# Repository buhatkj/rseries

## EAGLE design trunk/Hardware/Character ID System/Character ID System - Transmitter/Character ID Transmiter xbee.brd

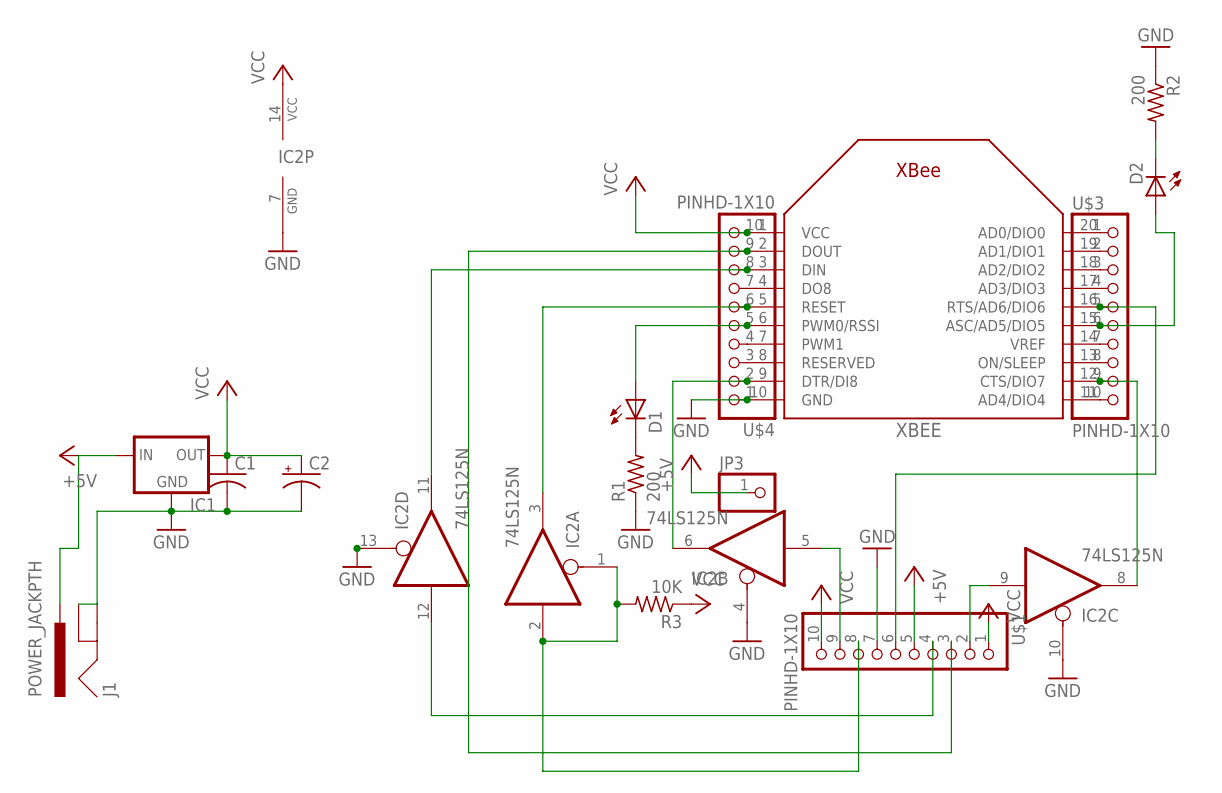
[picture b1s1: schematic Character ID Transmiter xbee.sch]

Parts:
C1: C-US025-025X050; C025-025X050
C2: CPOL-USE2.5-5; E2,5-5
D1, D2: LED3MM
IC1: MC1700; TO92
IC2: 74LS125N; DIL14
J1: POWER_JACKPTH; POWER_JACK_PTH
JP3: PINHD-1X1; 1X01
R1, R2: 200; 0207/10
R3: 10K; 0207/10
U$1, U$3, U$4: PINHD-1X10; 1X10-BIG
XBEE: XBEE

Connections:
+5V: IC1.2 (IN), J1.PWR, JP3.1, U$1.5
GND: C1.2, C2.-, IC1.1 (GND), IC2.4 (OE), IC2.7 (GND), IC2.10 (OE), IC2.13 (OE), J1.GND, J1.GNDBREAK, R1.1, R2.1, U$1.7, U$4.1, XBEE.10 (GND)
unnamed: IC2.12 (I), U$1.4
unnamed: IC2.11 (O), U$4.8, XBEE.3 (DIN)
unnamed: IC2.5 (I), U$1.9
unnamed: IC2.8 (O), U$3.9, XBEE.12 (CTS/DIO7)
unnamed: D2.K (C), R2.2
unnamed: U$4.7, XBEE.4 (DO8)
unnamed: D1.A, U$4.5, XBEE.6 (PWM0/RSSI)
unnamed: D1.K (C), R1.2
unnamed: D2.A, U$3.6, XBEE.15 (ASC/AD5/DIO5)
unnamed: IC2.6 (O), U$4.2, XBEE.9 (DTR/DI8)
unnamed: U$4.3, XBEE.8 (RESERVED)
unnamed: U$4.4, XBEE.7 (PWM1)
unnamed: IC2.3 (O), U$4.6, XBEE.5 (RESET)
unnamed: U$3.1, XBEE.20 (AD0/DIO0)
unnamed: U$3.2, XBEE.19 (AD1/DIO1)
unnamed: U$3.3, XBEE.18 (AD2/DIO2)
unnamed: U$3.4, XBEE.17 (AD3/DIO3)
unnamed: U$3.7, XBEE.14 (VREF)
unnamed: U$3.8, XBEE.13 (ON/SLEEP)
unnamed: U$3.10, XBEE.11 (AD4/DIO4)
unnamed: IC2.9 (I), U$1.2
RESET: IC2.1 (OE), IC2.2 (I), R3.2, U$1.8
RTS: U$1.6, U$3.5, XBEE.16 (RTS/AD6/DIO6)
TX: U$1.3, U$4.9, XBEE.2 (DOUT)
VCC: C1.1, C2.+, IC1.3 (OUT), IC2.14 (VCC), R3.1, U$1.1, U$1.10, U$4.10, XBEE.1 (VCC)

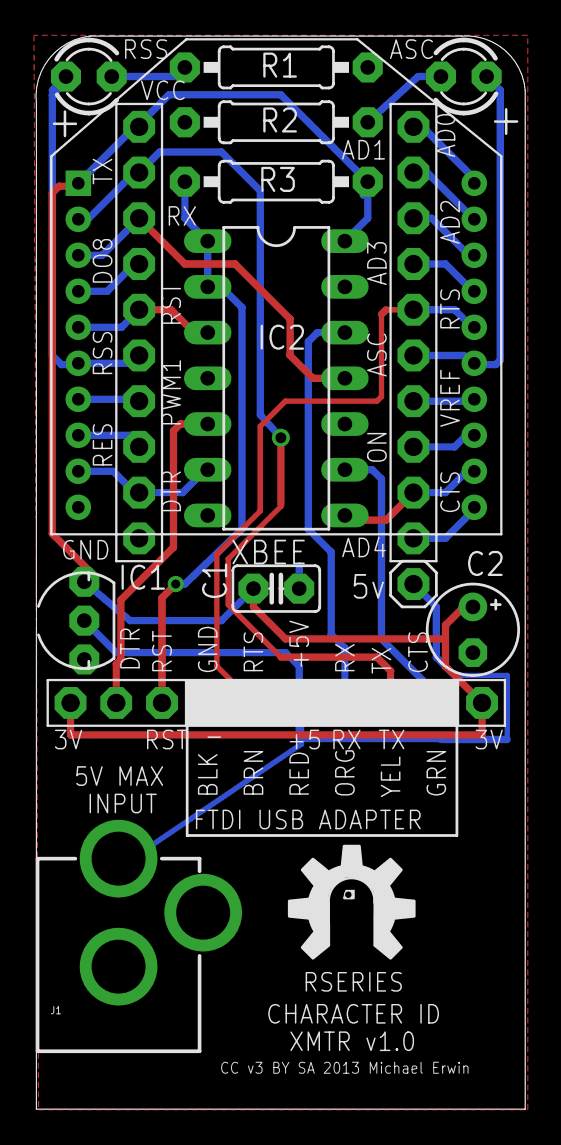
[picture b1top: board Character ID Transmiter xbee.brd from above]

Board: 2 copper layers, 27.2 x 59.6 mm, 17 parts (1 on the bottom side), 27 nets.

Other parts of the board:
U$2: RSERIES-OSHW-LOGO-LARGE
U$5: ROYAL-ENGINEERS-OF-NABOO-SMALL

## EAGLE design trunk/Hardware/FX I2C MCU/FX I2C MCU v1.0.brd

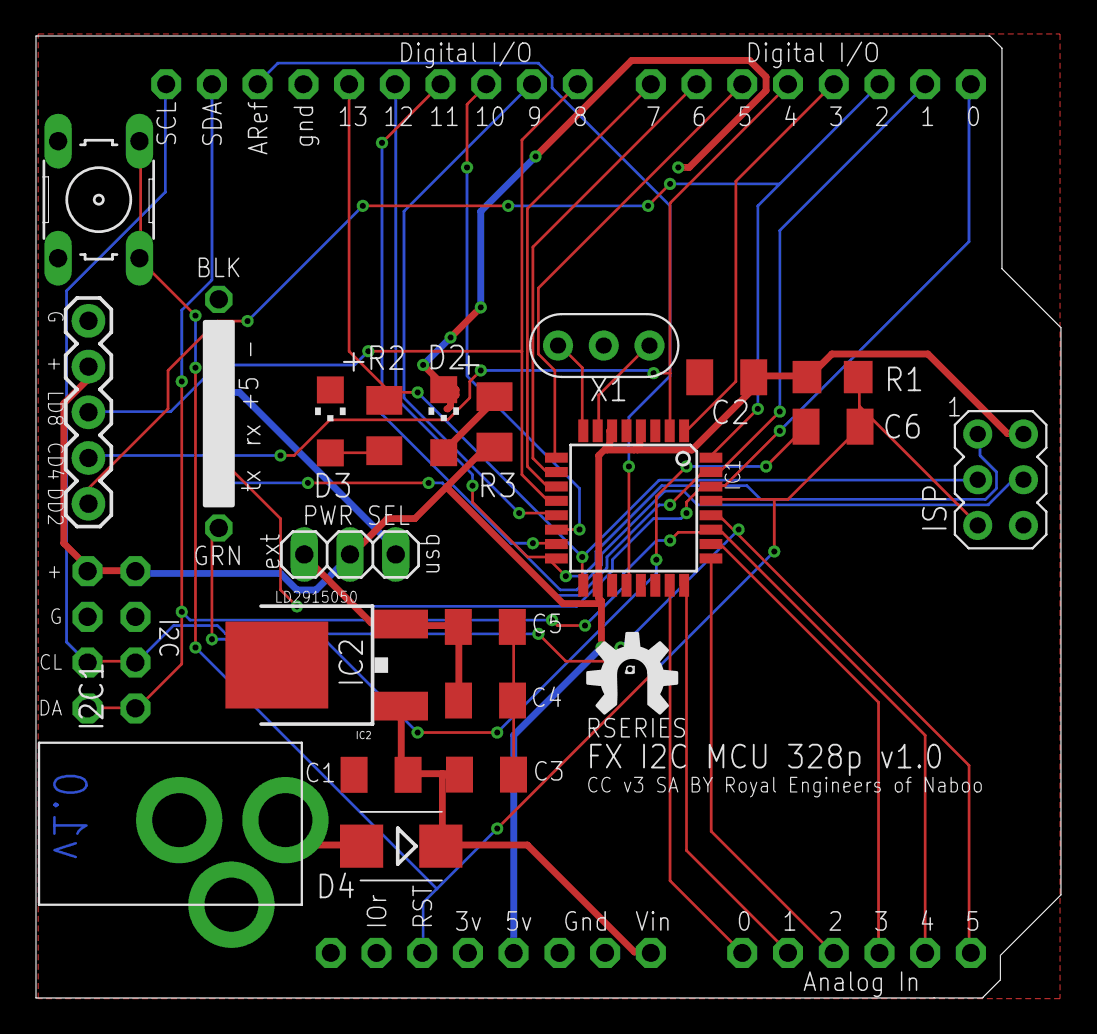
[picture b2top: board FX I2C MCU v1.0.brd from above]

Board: 2 copper layers, 56.9 x 53.4 mm, 25 parts (0 on the bottom side), 34 nets.

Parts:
C1, C2, C5, C6: 0.1uF; C1206K
C3, C4: 10uf 25V; C1206K
D2: CHIPLED_1206
D3: Green; CHIPLED_1206
D4: SMB
I2C, I2C1: 1X04-CB
IC1: MEGA48/88/168-AU; TQFP32-08
IC2: LM2931_FIXED; DPAK
ISP: AVRISP-6; AVRISP
J2: 2.1MMJACK; PJ-102A
JP7: 1X06-CLEAN
PWR_SEL: 1X03
R1: 10K; R1206
R2, R3: 1.0 K; M1206
S1: RESET; B3F-10XX
TEECES: 1X05
U1: ARDUINOR3PINSONLY; ARDUINOR3-PINSONLY
U$2: RSERIES-OSHW-LOGOMEDIUM; RSERIES-OSHW-LOGO-MEDIUM
X1: 16.00MHz; CERM_OSC

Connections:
+5V: C2.1, I2C.4, I2C1.4, IC1.4, IC1.6, IC1.18, ISP.2, PWR_SEL.2, R1.1, R3.1, TEECES.4, U1.5V
+9V: C1.1, C3.1, D4.C, IC2.1, U1.VIN
ANALOG0: IC1.23, U1.A0
ANALOG1: IC1.24, U1.A1
ANALOG2: IC1.25, U1.A2
ANALOG3: IC1.26, U1.A3
ANALOG4: I2C.1, I2C1.1, IC1.27, U1.A4, U1.SDA
ANALOG5: I2C.2, I2C1.2, IC1.28, U1.A5, U1.SCL
AREF: IC1.20, U1.AREF
DIGITAL2: IC1.32, TEECES.1, U1.D2
DIGITAL3: IC1.1, U1.D3
DIGITAL4: IC1.2, TEECES.2, U1.D4
DIGITAL5: IC1.9, U1.D5
DIGITAL6: IC1.10, U1.D6
DIGITAL7: IC1.11, U1.D7
DIGITAL8: IC1.12, TEECES.3, U1.D8
DIGITAL9: IC1.13, U1.D9
DIGITAL10: IC1.14, U1.D10
GND: C1.2, C2.2, D2.C, D3.C, I2C.3, I2C1.3, IC1.3, IC1.5, IC1.21, IC2.4, ISP.6, J2.RING, JP7.1, JP7.2, S1.1, S1.2, TEECES.5, U1.GND, U1.GND1, U1.GND2, X1.P$2
MISO: IC1.16, ISP.1, U1.D12
MOSI: IC1.15, ISP.4, U1.D11
unnamed: IC1.7, X1.P$1
unnamed: IC1.8, X1.P$3
unnamed: D2.A, R3.2
unnamed: D3.A, R2.2
unnamed: D4.A, J2.TIP
unnamed: C3.2, C4.2, C5.2
unnamed: C4.1, C5.1, IC2.3, PWR_SEL.1
RST: C6.2, IC1.29, ISP.5, R1.2, S1.3, S1.4, U1.RESET
RTS#: C6.1, JP7.6
RXD: IC1.30, JP7.4, U1.D0
SCK: IC1.17, ISP.3, R2.1, U1.D13
TXD: IC1.31, JP7.5, U1.D1
USB_5V: JP7.3, PWR_SEL.3

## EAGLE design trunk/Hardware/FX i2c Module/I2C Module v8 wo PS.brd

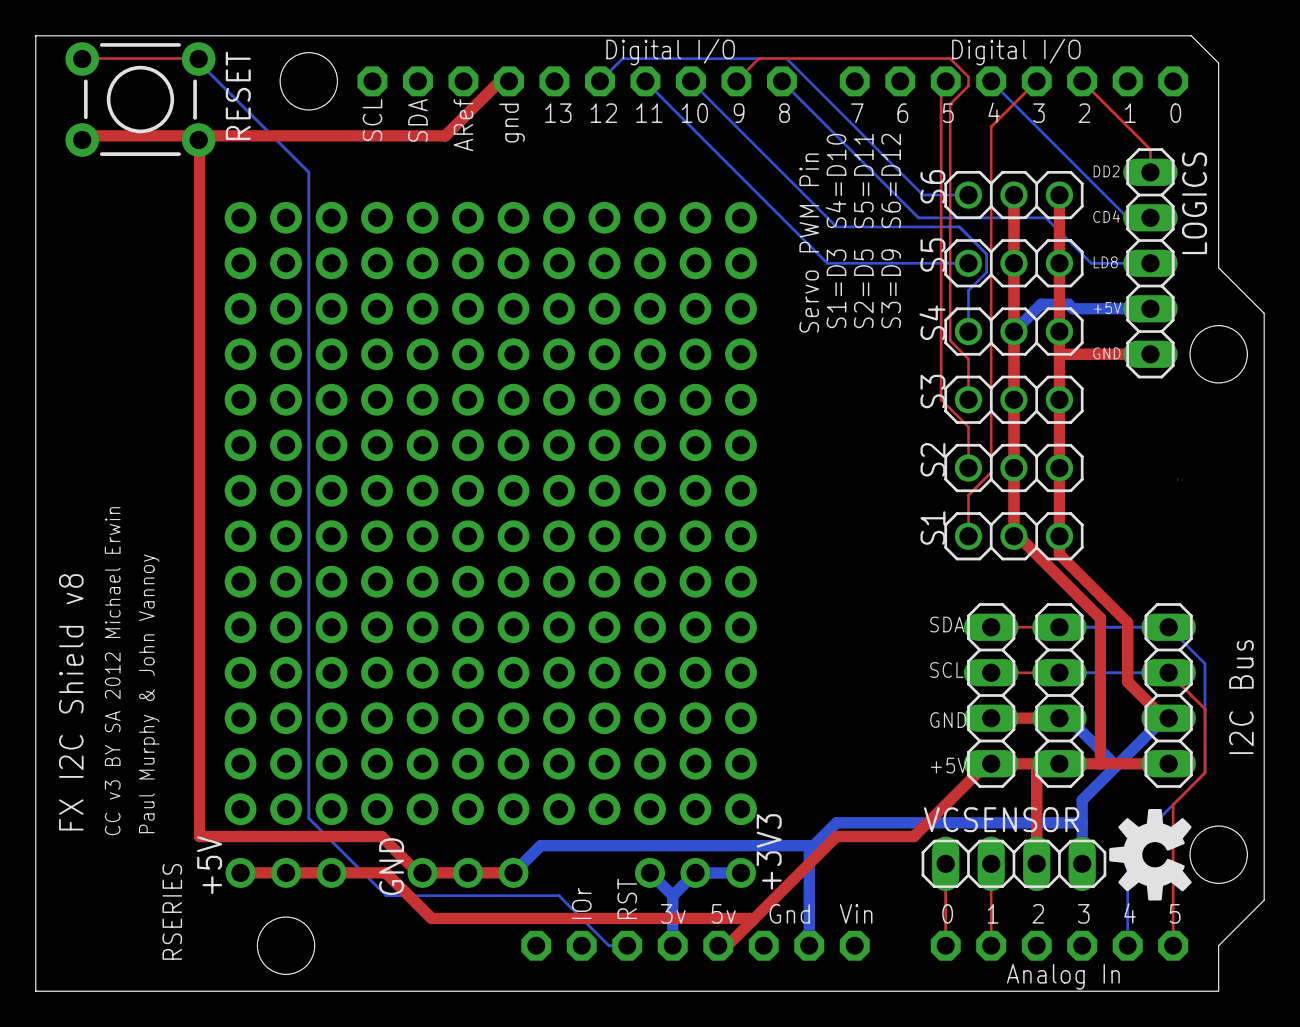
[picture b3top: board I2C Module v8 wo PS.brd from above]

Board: 2 copper layers, 68.6 x 53.3 mm, 31 parts (0 on the bottom side), 17 nets.

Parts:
+3V3, +5V: 1X03-CLEANBIG
GND: 1X03-CLEANBIG
I2C3: 1X04
JP1, JP2: 1X04
JP3, JP4, JP5, JP6, JP7, JP8, JP9, JP10, JP11, JP12, JP13, JP14, JP15, JP16: 1X12-CB
LOGICS: 1X05
RESET: TACTILE-PTH
S1, S2, S3, S4, S5, S6: 1X03
U1: ARDUINOR3-DIMENSION; ARDUINOR3
U$1: OSHW-LOGOM; OSHW-LOGO-M
VCSENSOR: 1X04

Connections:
+3V3: +3V3.1, +3V3.2, +3V3.3, U1.3V
+5V: +5V.1, +5V.2, +5V.3, I2C3.4, JP1.4, JP2.4, LOGICS.4, S1.2, S2.2, S3.2, S4.2, S5.2, S6.2, U1.5V, VCSENSOR.3
GND: GND.1, GND.2, GND.3, I2C3.3, JP1.3, JP2.3, LOGICS.5, RESET.1, RESET.2, S1.3, S2.3, S3.3, S4.3, S5.3, S6.3, U1.GND, U1.GND1, VCSENSOR.4
unnamed: U1.A0, VCSENSOR.1
unnamed: LOGICS.3, U1.D8
unnamed: U1.A1, VCSENSOR.2
unnamed: S1.1, U1.D3
unnamed: S2.1, U1.D5
unnamed: S3.1, U1.D9
unnamed: S4.1, U1.D10
unnamed: S5.1, U1.D11
unnamed: S6.1, U1.D12
unnamed: LOGICS.2, U1.D4
unnamed: LOGICS.1, U1.D2
unnamed: RESET.3, RESET.4, U1.RESET
unnamed: I2C3.2, JP1.2, JP2.2, U1.A5
unnamed: I2C3.1, JP1.1, JP2.1, U1.A4

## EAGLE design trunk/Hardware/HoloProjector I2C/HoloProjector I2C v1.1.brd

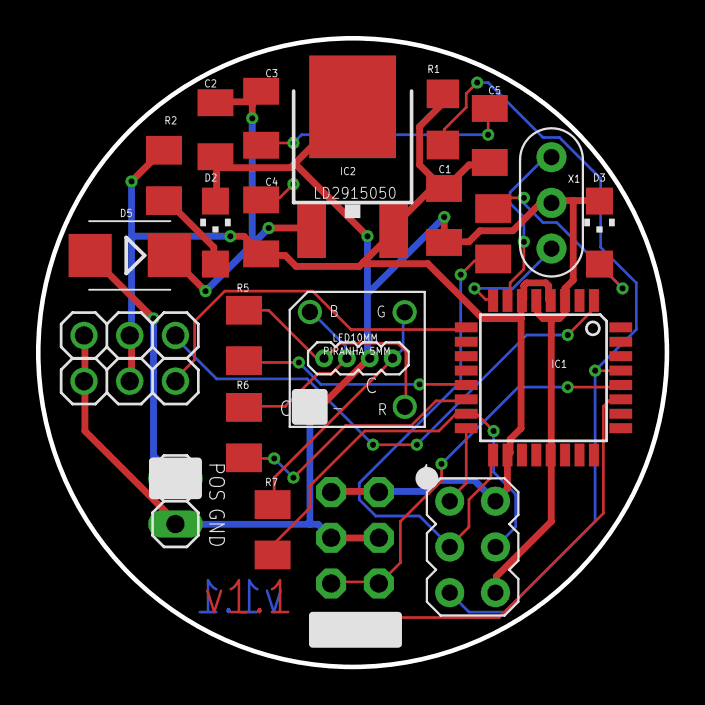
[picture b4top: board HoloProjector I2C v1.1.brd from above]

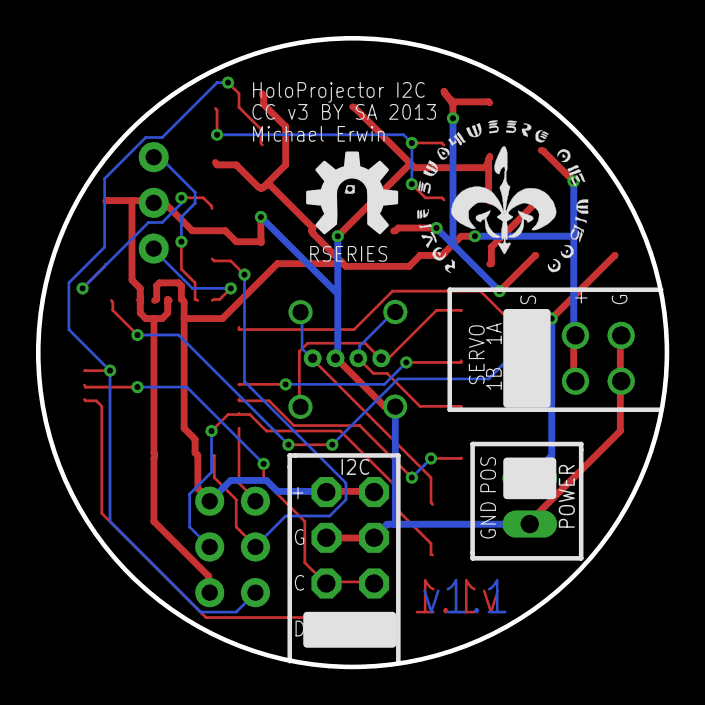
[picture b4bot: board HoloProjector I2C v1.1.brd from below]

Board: 2 copper layers, 34.9 x 34.9 mm, 27 parts (2 on the bottom side), 22 nets.

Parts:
C1, C2, C5: 0.1uF; C1206K
C3, C4: 10uf 25V; C1206K
D2: CHIPLED_1206
D3: Green; CHIPLED_1206
D5: SMB
I2C, I2C1: 1X04-CB
IC1: MEGA48/88/168-AU; TQFP32-08
IC2: LM2931_FIXED; DPAK
ICSP: AVRISP-6; AVRISP
JP1, JP2: 1X03
LED: LED_PIRANHA_5MM
LED10MM: 1X04-1.27MM
POWER: 1X02
R1: 10K; R1206
R2, R3: 1.0 K; M1206
R5, R6, R7: M1206
U$2: RSERIES-OSHW-LOGOMEDIUM; RSERIES-OSHW-LOGO-MEDIUM
U$3: ROYAL-ENGINEERS-OF-NABOOSMALL; ROYAL-ENGINEERS-OF-NABOO-SMALL
X1: 16.00MHz; CERM_OSC

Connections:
+5V: C1.1, C4.1, C5.1, I2C.4, I2C1.4, IC1.4, IC1.6, IC1.18, IC2.3, ICSP.2, JP1.2, JP2.2, R1.1, R2.1
+9V: C2.1, C3.1, D5.C, IC2.1
ANALOG4: I2C.1, I2C1.1, IC1.27
ANALOG5: I2C.2, I2C1.2, IC1.28
DIGITAL3: IC1.1, JP1.1
DIGITAL5: IC1.9, JP2.1
DIGITAL9: IC1.13, R5.2
DIGITAL10: IC1.14, R6.2
GND: C1.2, C2.2, D2.C, D3.C, I2C.3, I2C1.3, IC1.3, IC1.5, IC1.21, IC2.4, ICSP.6, JP1.3, JP2.3, LED.-, LED10MM.3, POWER.1, X1.P$2
MISO: IC1.16, ICSP.1
MOSI: IC1.15, ICSP.4, R7.2
unnamed: IC1.7, X1.P$1
unnamed: IC1.8, X1.P$3
unnamed: LED.R, LED10MM.1, R5.1
unnamed: D3.A, R3.2
unnamed: D2.A, R2.2
unnamed: D5.A, POWER.2
unnamed: LED.B, LED10MM.2, R6.1
unnamed: C3.2, C4.2, C5.2
unnamed: LED.G, LED10MM.4, R7.1
RST: IC1.29, ICSP.5, R1.2
SCK: IC1.17, ICSP.3, R3.1

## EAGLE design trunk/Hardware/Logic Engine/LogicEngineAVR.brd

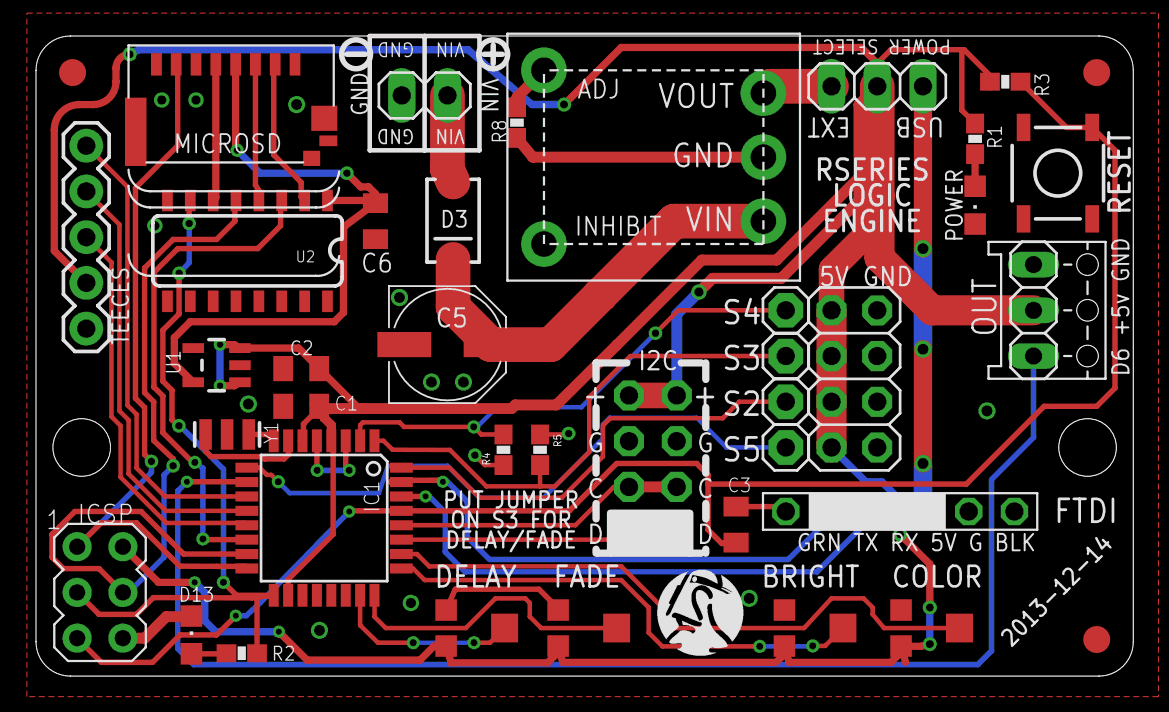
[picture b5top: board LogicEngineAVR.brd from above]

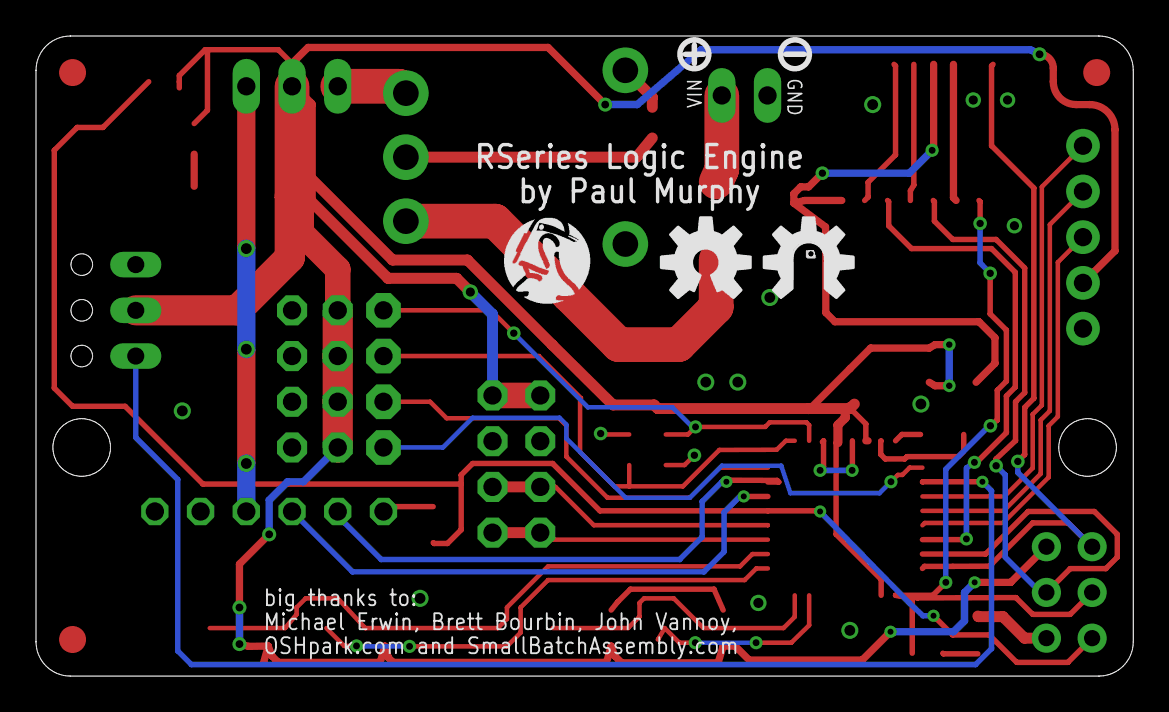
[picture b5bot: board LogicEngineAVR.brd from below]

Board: 2 copper layers, 61.0 x 35.6 mm, 45 parts (3 on the bottom side), 37 nets.

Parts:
BRIGHT: 10K; EVM3V
C1, C2, C3: 0.1uF; C0805K
C5: 100uF; PANASONIC_D
C6: 10uF; C0805K
COLOR: 10K; EVM3V
D3: BA340LA; SMA-DIODE
D13: RED; CHIPLED_0805
DELAY: 10K; EVM3V
EXT_PWR: 1X02
FADE: 10K; EVM3V
FID4, FID5, FID6: FIDUCIAL_G15
FTDI: GRN TX RX 5V G BLK; 1X06-CLEAN
I2C, I2C1: 1X04-CB
IC1: MEGA328P; TQFP32-08
ICSP: AVRISP-6; AVRISP
JP1: 2X04
MICROSD: MICROSD; MICROSD_SMALL
OUT: MDF7_1X03
POWER: GREEN; CHIPLED_0805
PWR_SEL1: 1X03
R1, R2: 1K; 0603-RES
R3, R4, R5: 10K; 0603-RES
R8: 348; 0603-RES
REG: PTH08080W; PTH08080W_TH
RESET: RST; TACTILE_SWITCH_SMD
S2, S3, S4, S5: 1X01
TEECES: G +5V D9 D8 D7; 1X05
U1: LP2985; SOT23-5
U2: HEX_CONVERTER; SO016
U$1: OSHW-LOGO-M
U$3: RSERIES-OSHW-LOGO-MEDIUM-BOTTOM
U$4, U$5: R2BUILDERS-LOGO
Y1: 16MHz; RESONATOR-SMD

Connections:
+5V: BRIGHT.3, C1.1, C2.1, COLOR.3, DELAY.3, FADE.3, I2C.4, I2C1.4, IC1.4, IC1.6, IC1.18, ICSP.2, JP1.1, JP1.3, JP1.5, JP1.7, OUT.2, PWR_SEL1.2, R1.1, R3.1, TEECES.2, U1.1, U1.3
ANALOG0: DELAY.2, IC1.23
ANALOG1: FADE.2, IC1.24
ANALOG2: BRIGHT.2, IC1.25
ANALOG3: COLOR.2, IC1.26
ANALOG4: I2C.1, I2C1.1, IC1.27
ANALOG5: I2C.2, I2C1.2, IC1.28
DIGITAL2: IC1.32, S2.1
DIGITAL3: IC1.1, R5.2, S3.1
DIGITAL4: IC1.2, R4.2, S4.1
DIGITAL5: IC1.9, S5.1
DIGITAL6: IC1.10, OUT.3
DIGITAL7: IC1.11, TEECES.5
DIGITAL8: IC1.12, TEECES.4
DIGITAL9: IC1.13, TEECES.3
DIGITAL10: IC1.14, U2.3
GND: BRIGHT.1, C1.2, C2.2, C5.-, C6.2, COLOR.1, D13.C, DELAY.1, EXT_PWR.1, FADE.1, FTDI.1, FTDI.2, I2C.3, I2C1.3, IC1.3, IC1.5, IC1.21, ICSP.6, JP1.2, JP1.4, JP1.6, JP1.8, MICROSD.6, MICROSD.MT1, MICROSD.MT2, OUT.1, POWER.C, R4.1, R5.1, R8.1, REG.GND, RESET.3, TEECES.1, U1.2, U2.8, Y1.2
MISO: IC1.16, ICSP.1, MICROSD.7
MOSI: IC1.15, ICSP.4, U2.5
unnamed: IC1.7, Y1.1
unnamed: IC1.8, Y1.3
unnamed: C5.+, D3.C, REG.VIN
unnamed: D13.A, R2.2
unnamed: POWER.A, R1.2
unnamed: R8.2, REG.ADJ
unnamed: D3.A, EXT_PWR.2
unnamed: MICROSD.3, U2.4
unnamed: MICROSD.5, U2.6
unnamed: MICROSD.2, U2.2
unnamed: PWR_SEL1.1, REG.VOUT
RST: C3.2, IC1.29, ICSP.5, R3.2, RESET.1
RTS#: C3.1, FTDI.6
RXD: FTDI.4, IC1.30
SCK: IC1.17, ICSP.3, R2.1, U2.7
TXD: FTDI.5, IC1.31
USB_5V: FTDI.3, PWR_SEL1.3
VDD: C6.1, MICROSD.4, U1.5, U2.1

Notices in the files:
parts and their libraries:
SparkFun-Connectors: Licensing: CC v3.0 Share-Alike You are welcome to use this library for commercial purposes.
